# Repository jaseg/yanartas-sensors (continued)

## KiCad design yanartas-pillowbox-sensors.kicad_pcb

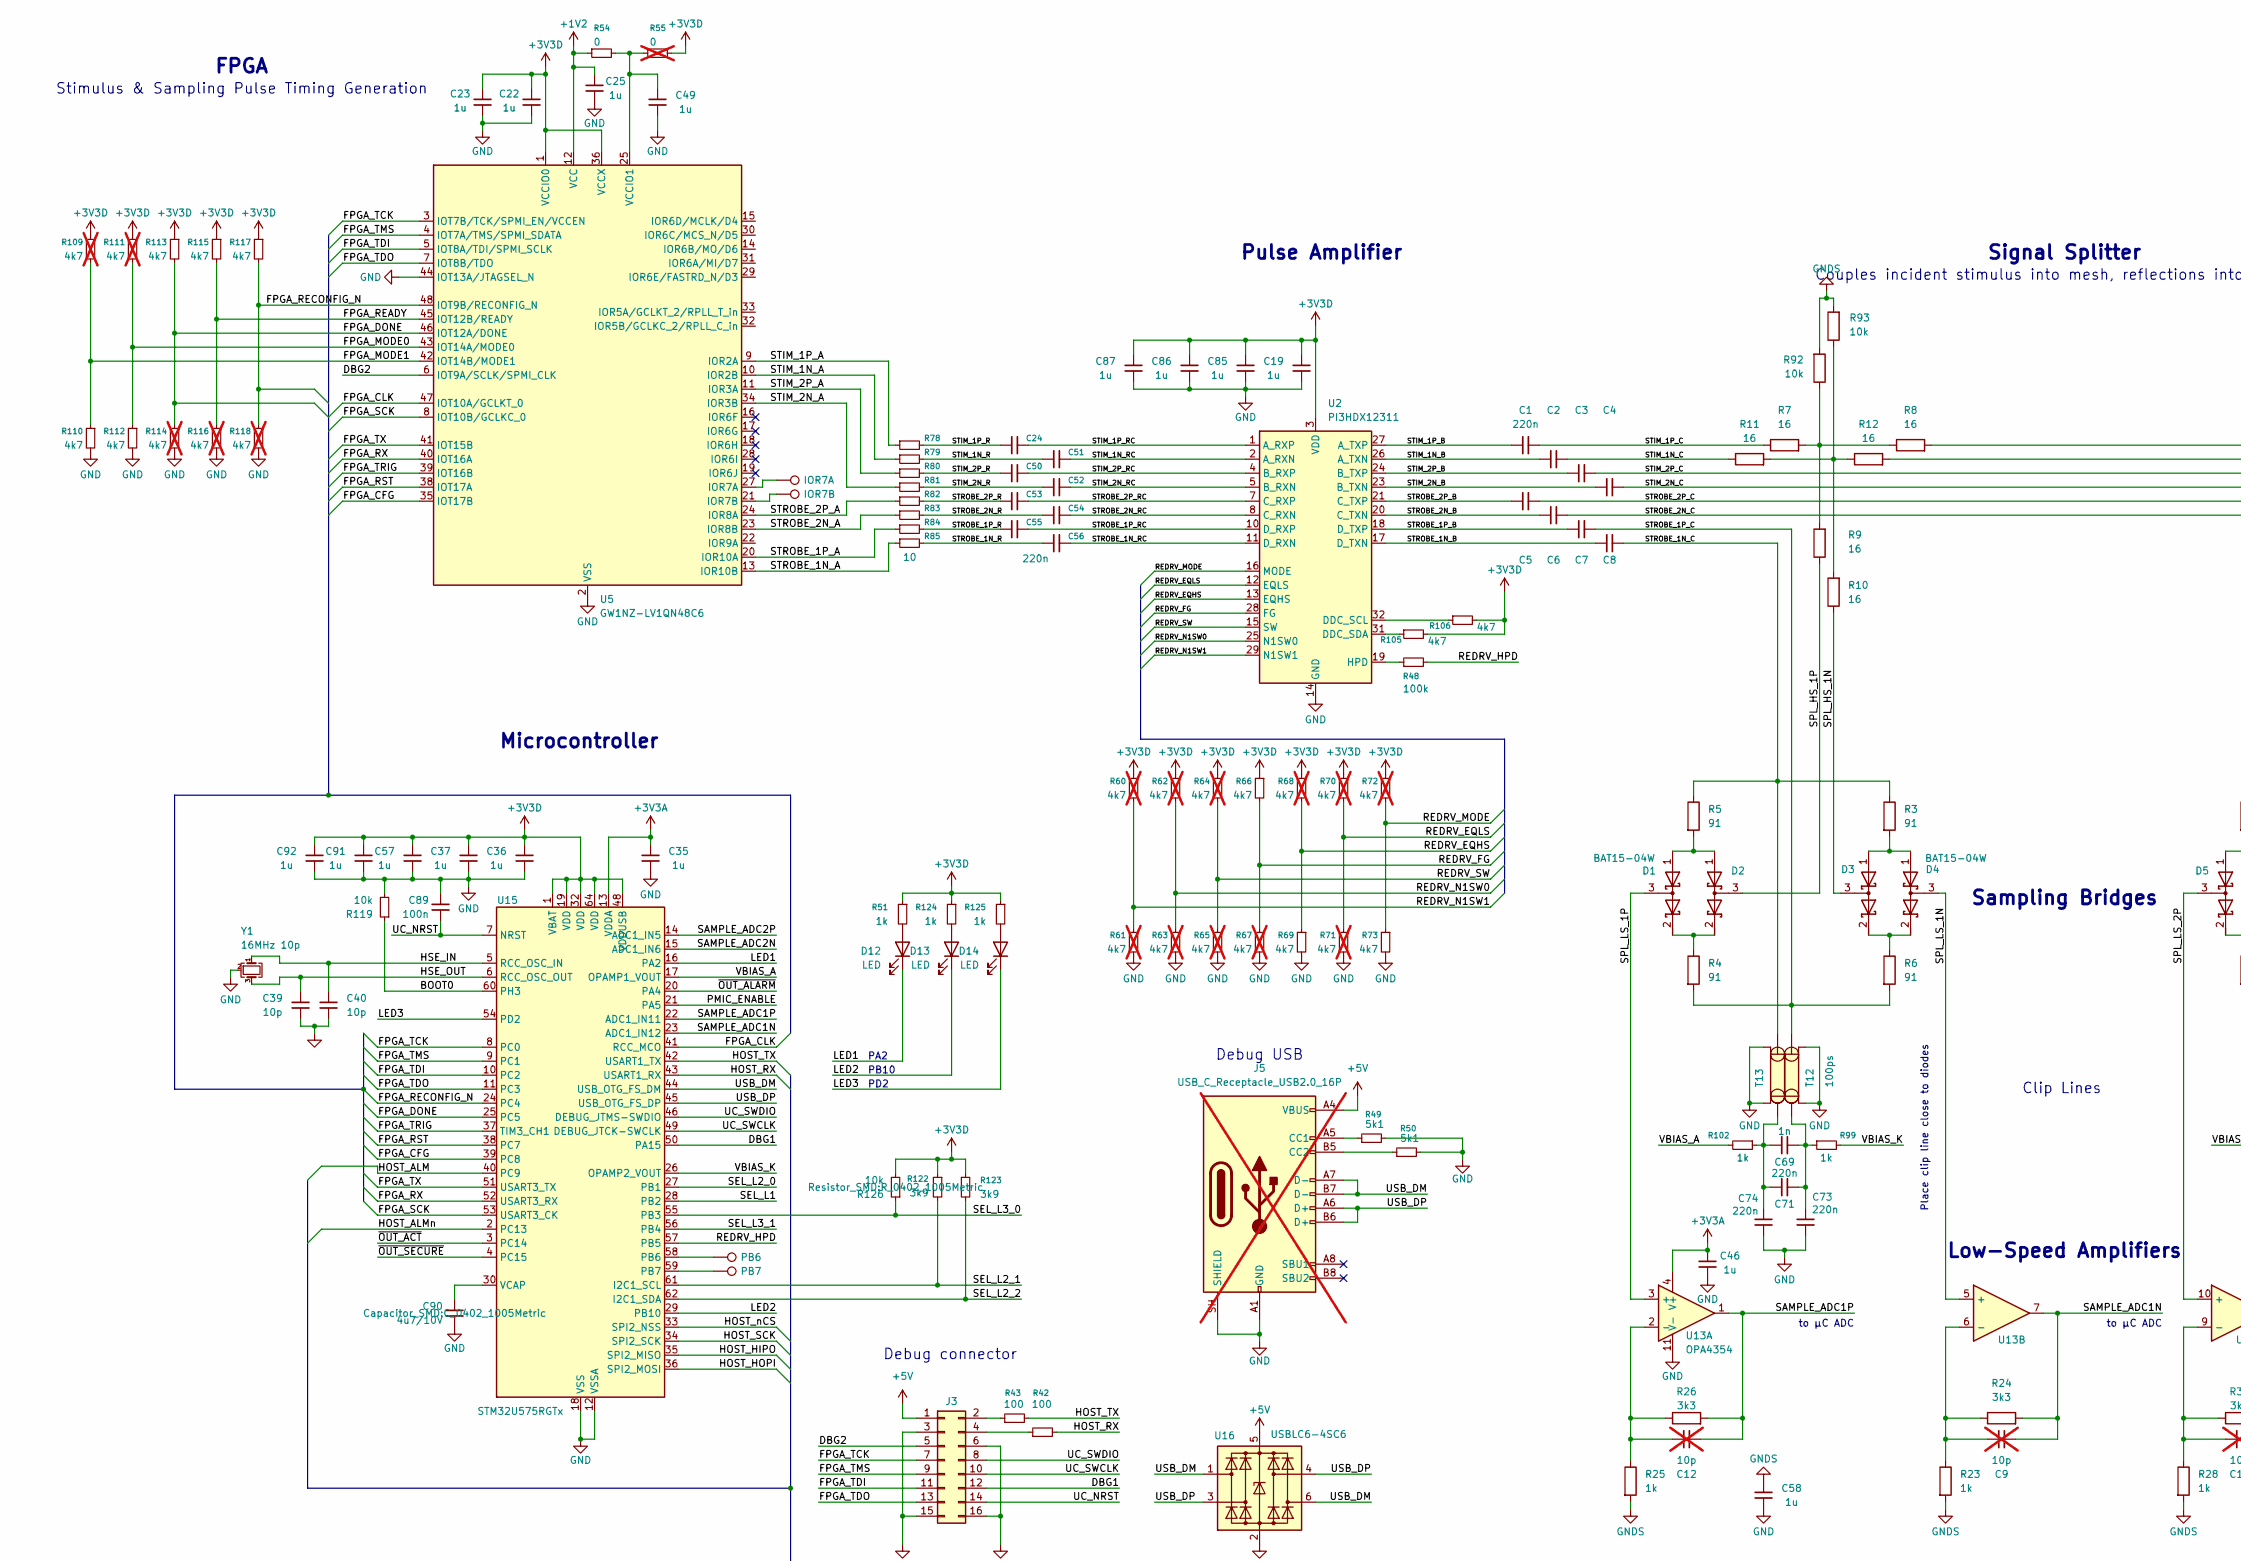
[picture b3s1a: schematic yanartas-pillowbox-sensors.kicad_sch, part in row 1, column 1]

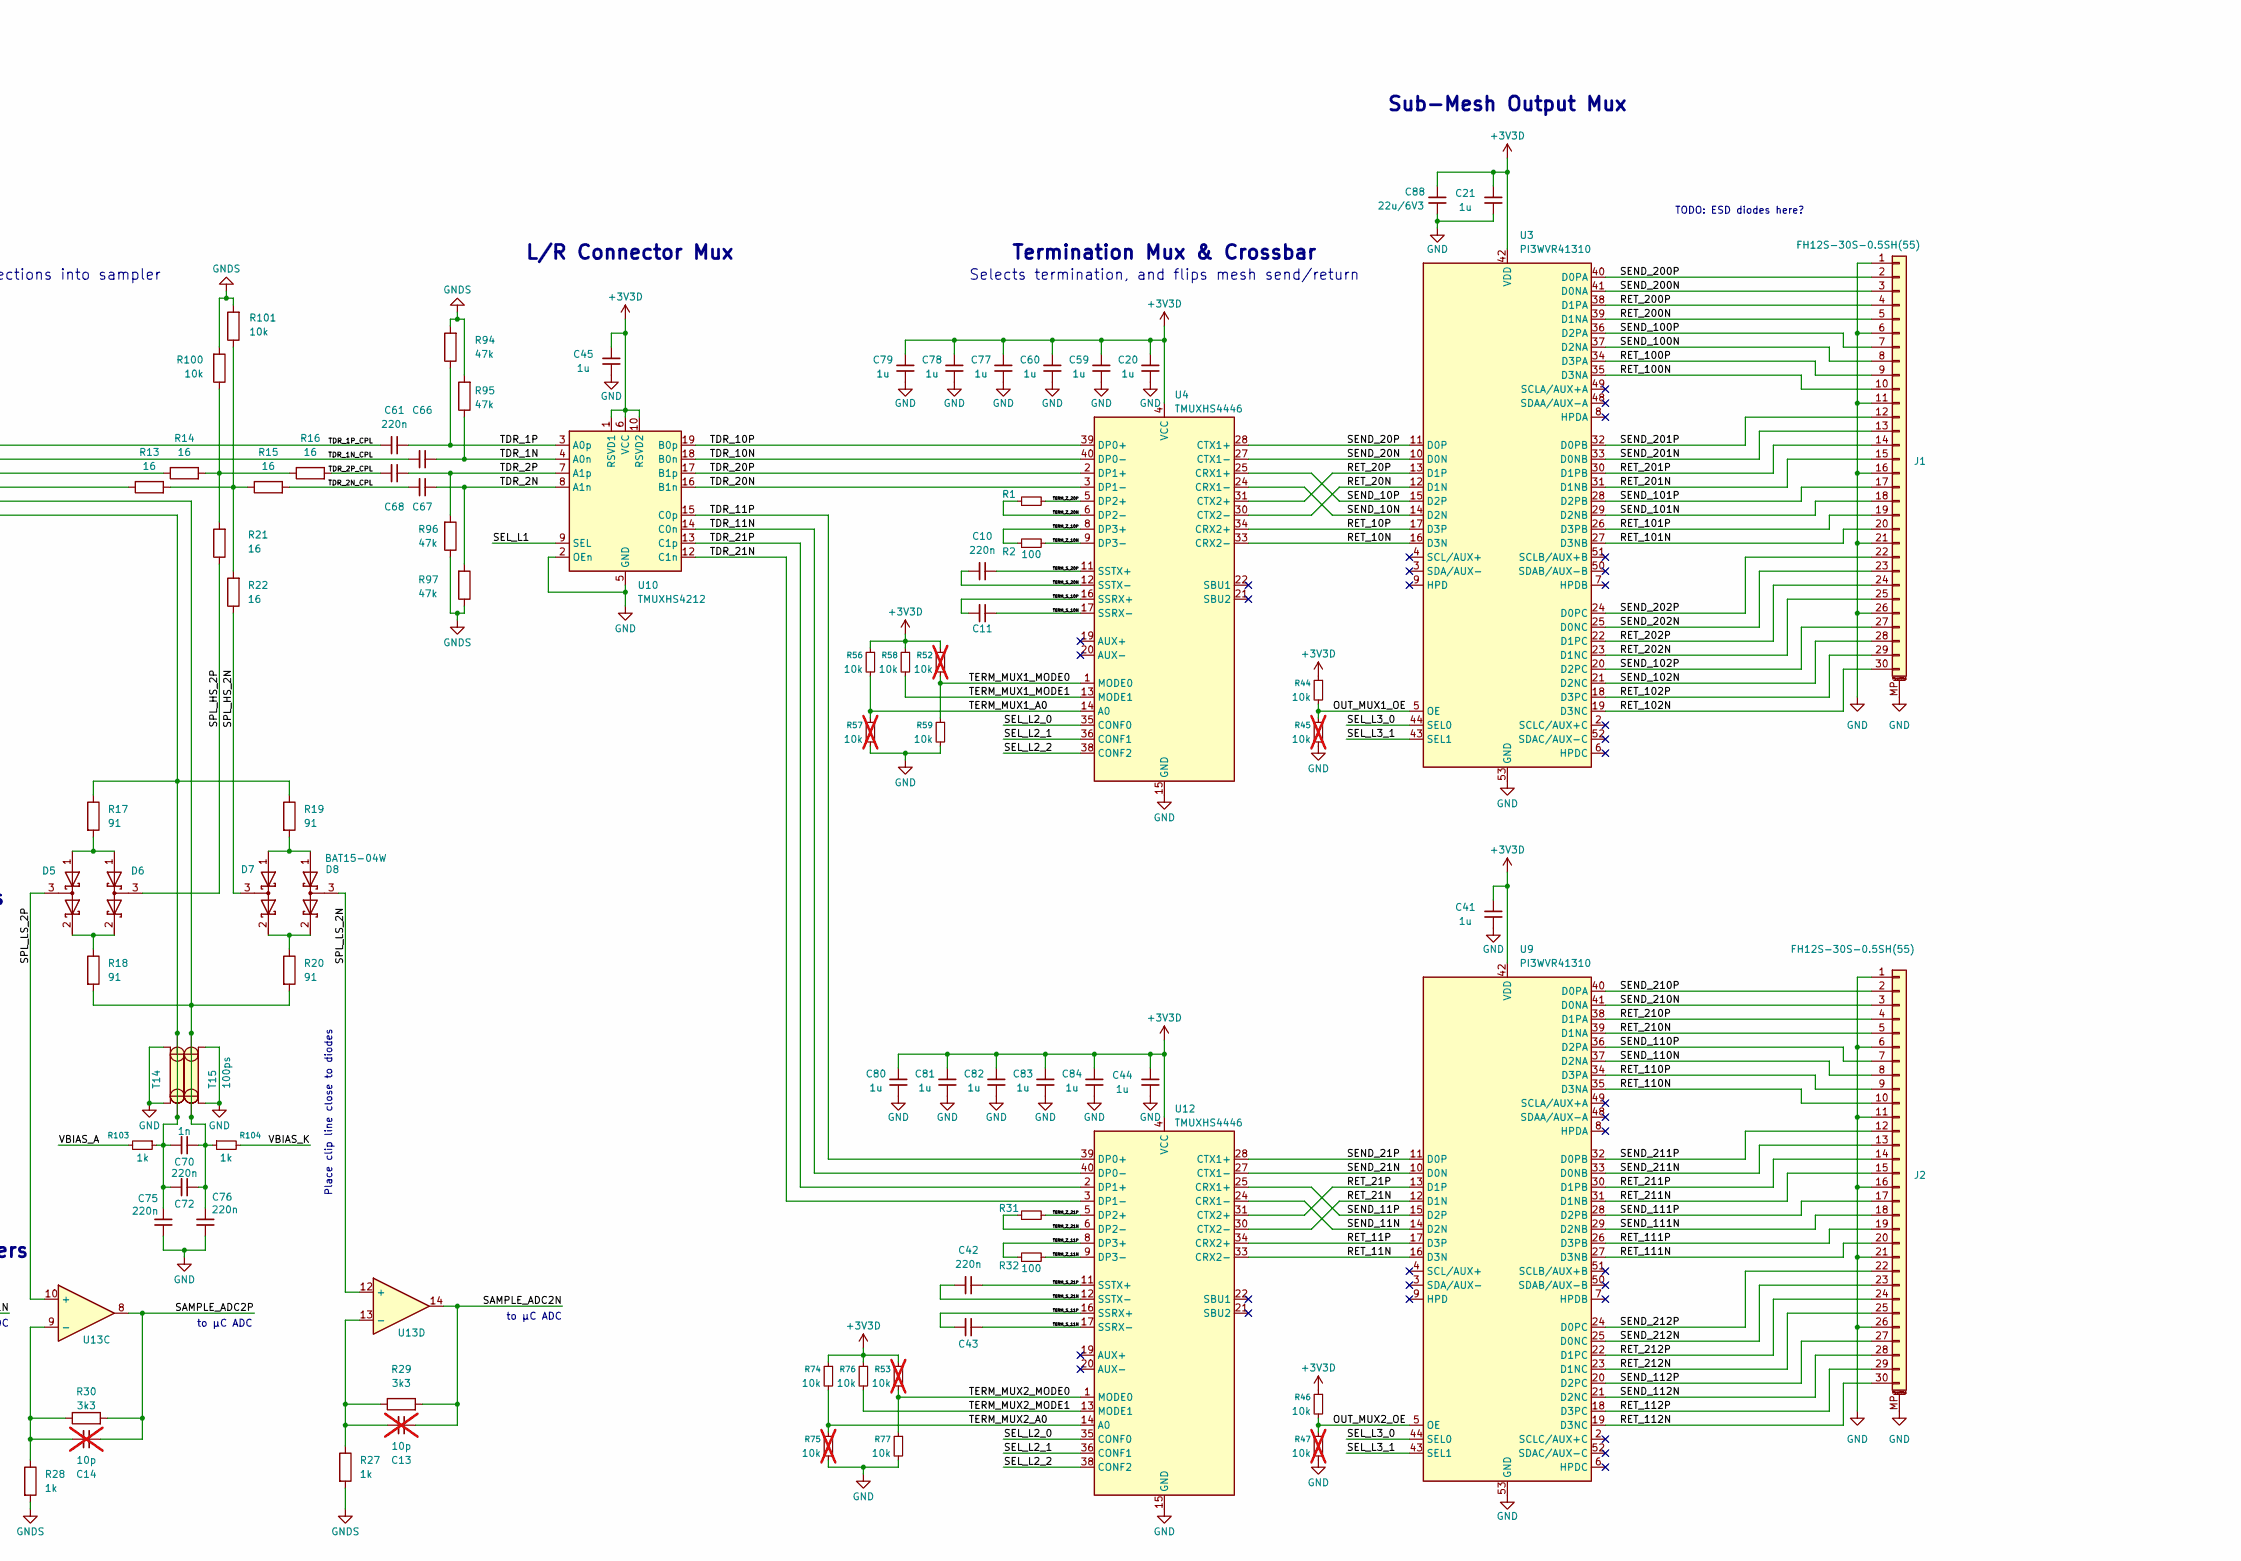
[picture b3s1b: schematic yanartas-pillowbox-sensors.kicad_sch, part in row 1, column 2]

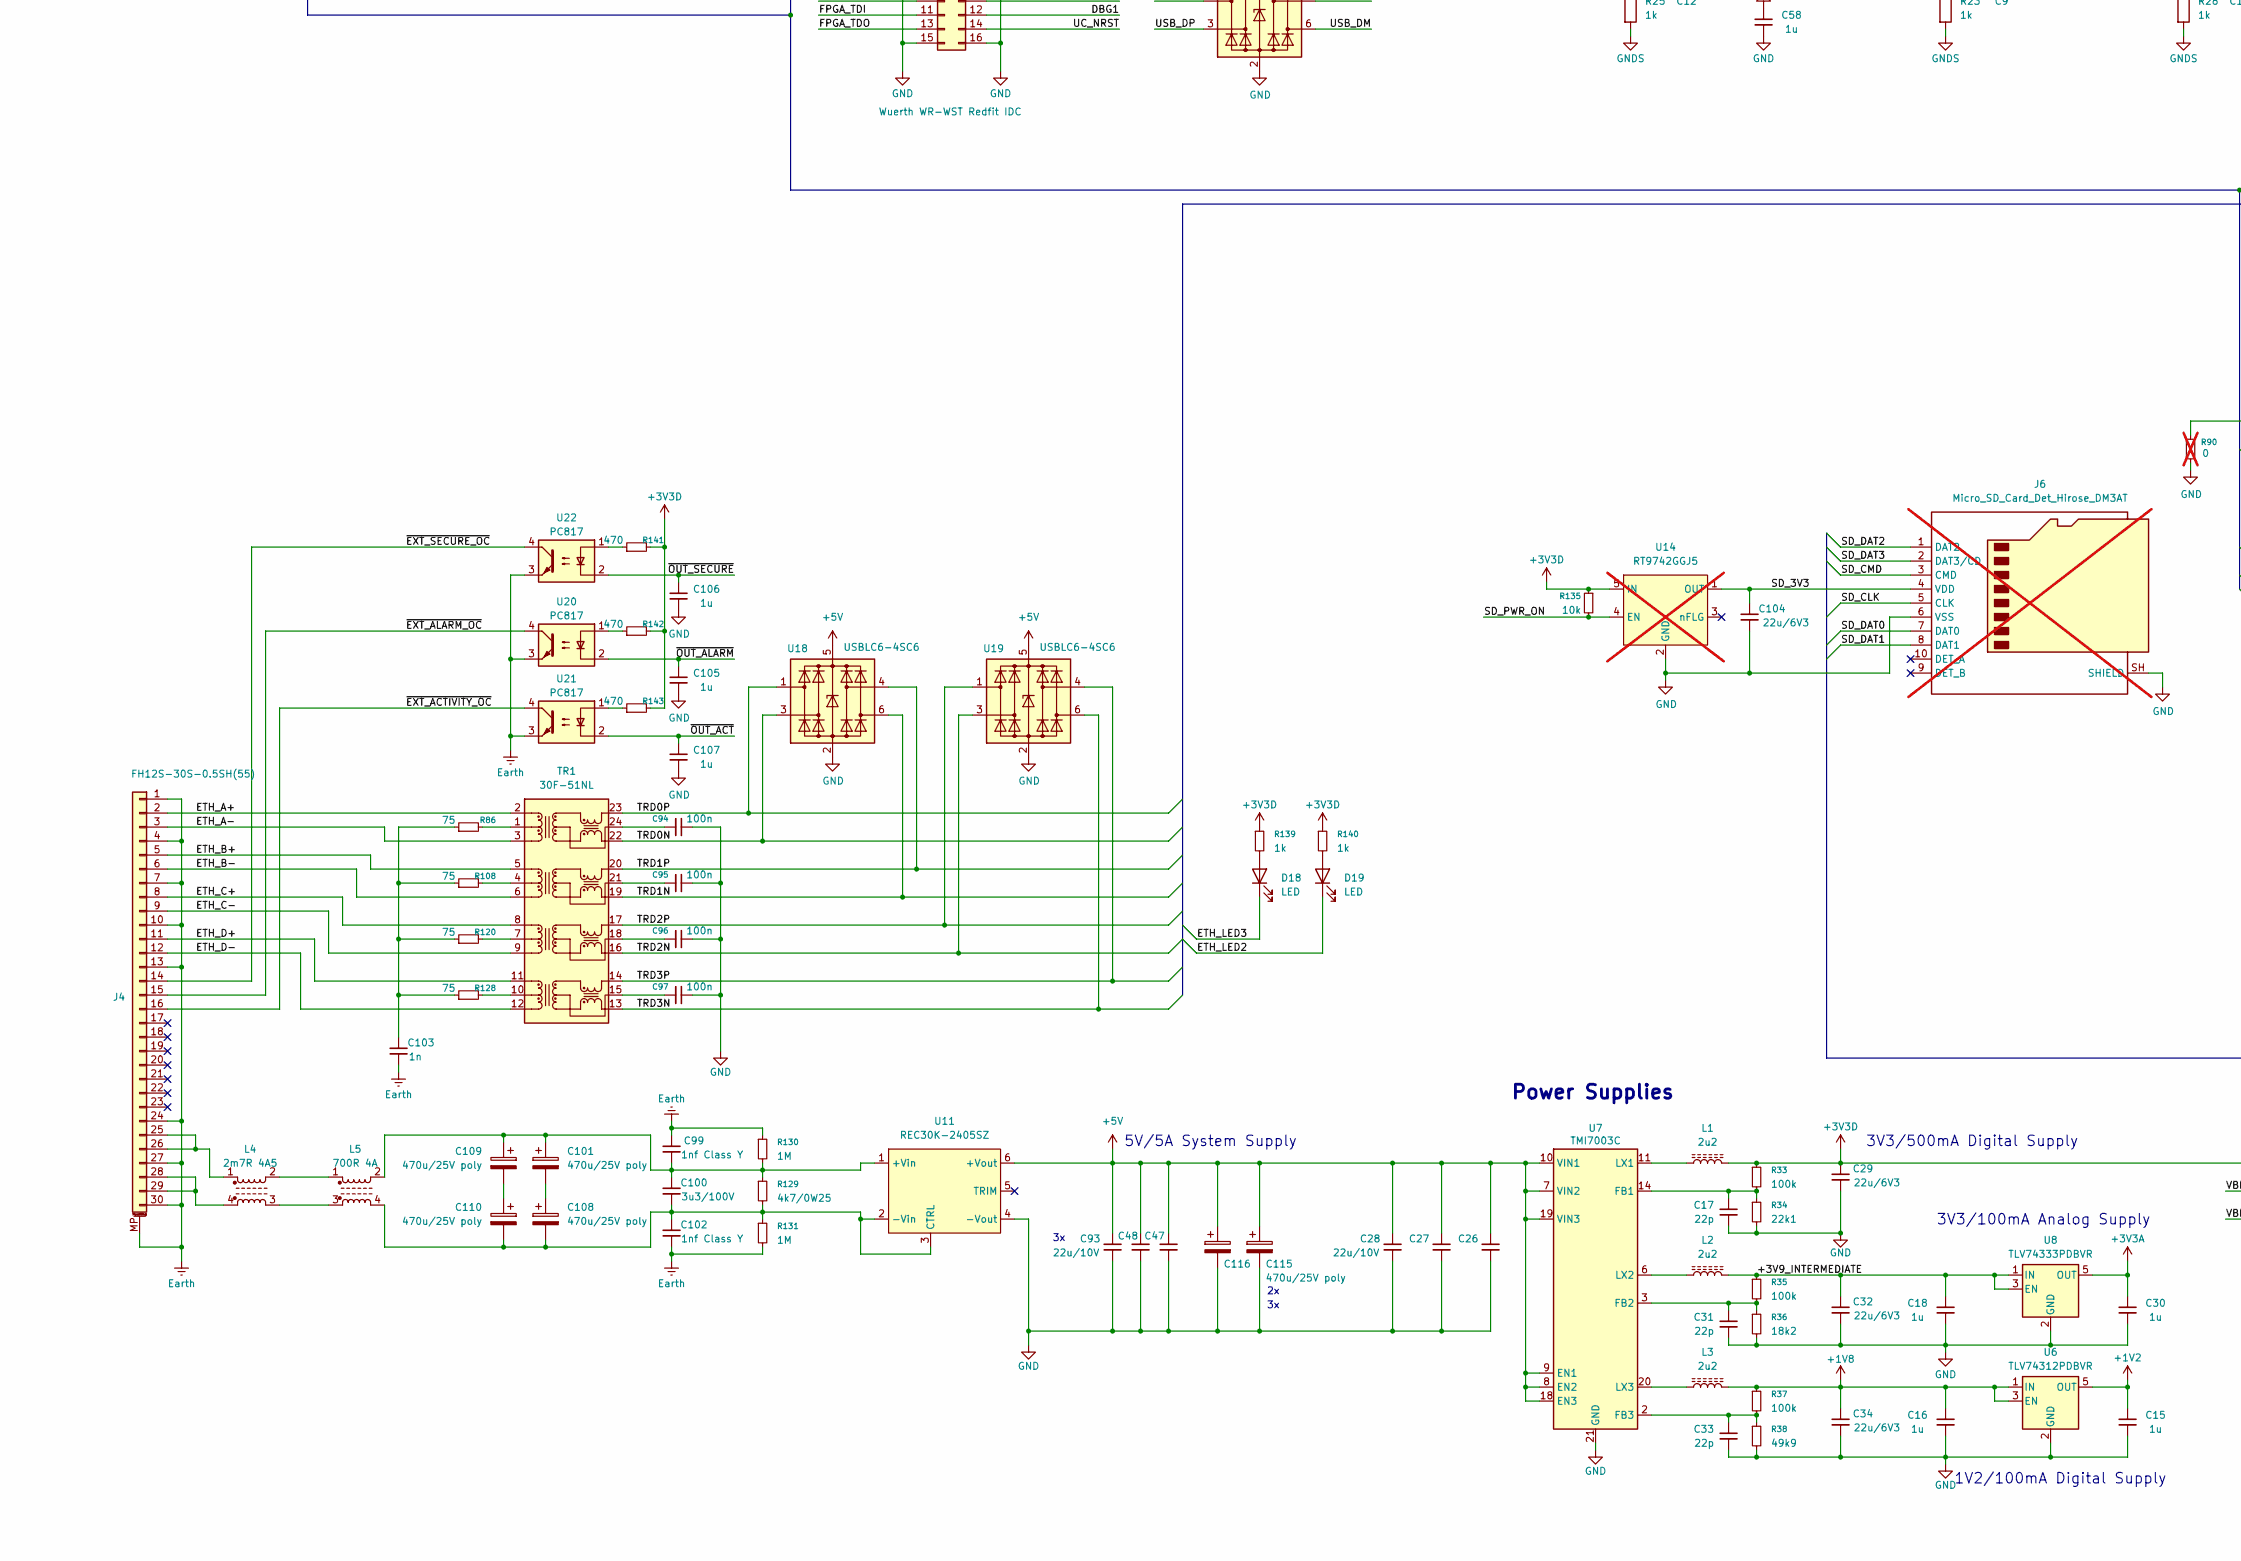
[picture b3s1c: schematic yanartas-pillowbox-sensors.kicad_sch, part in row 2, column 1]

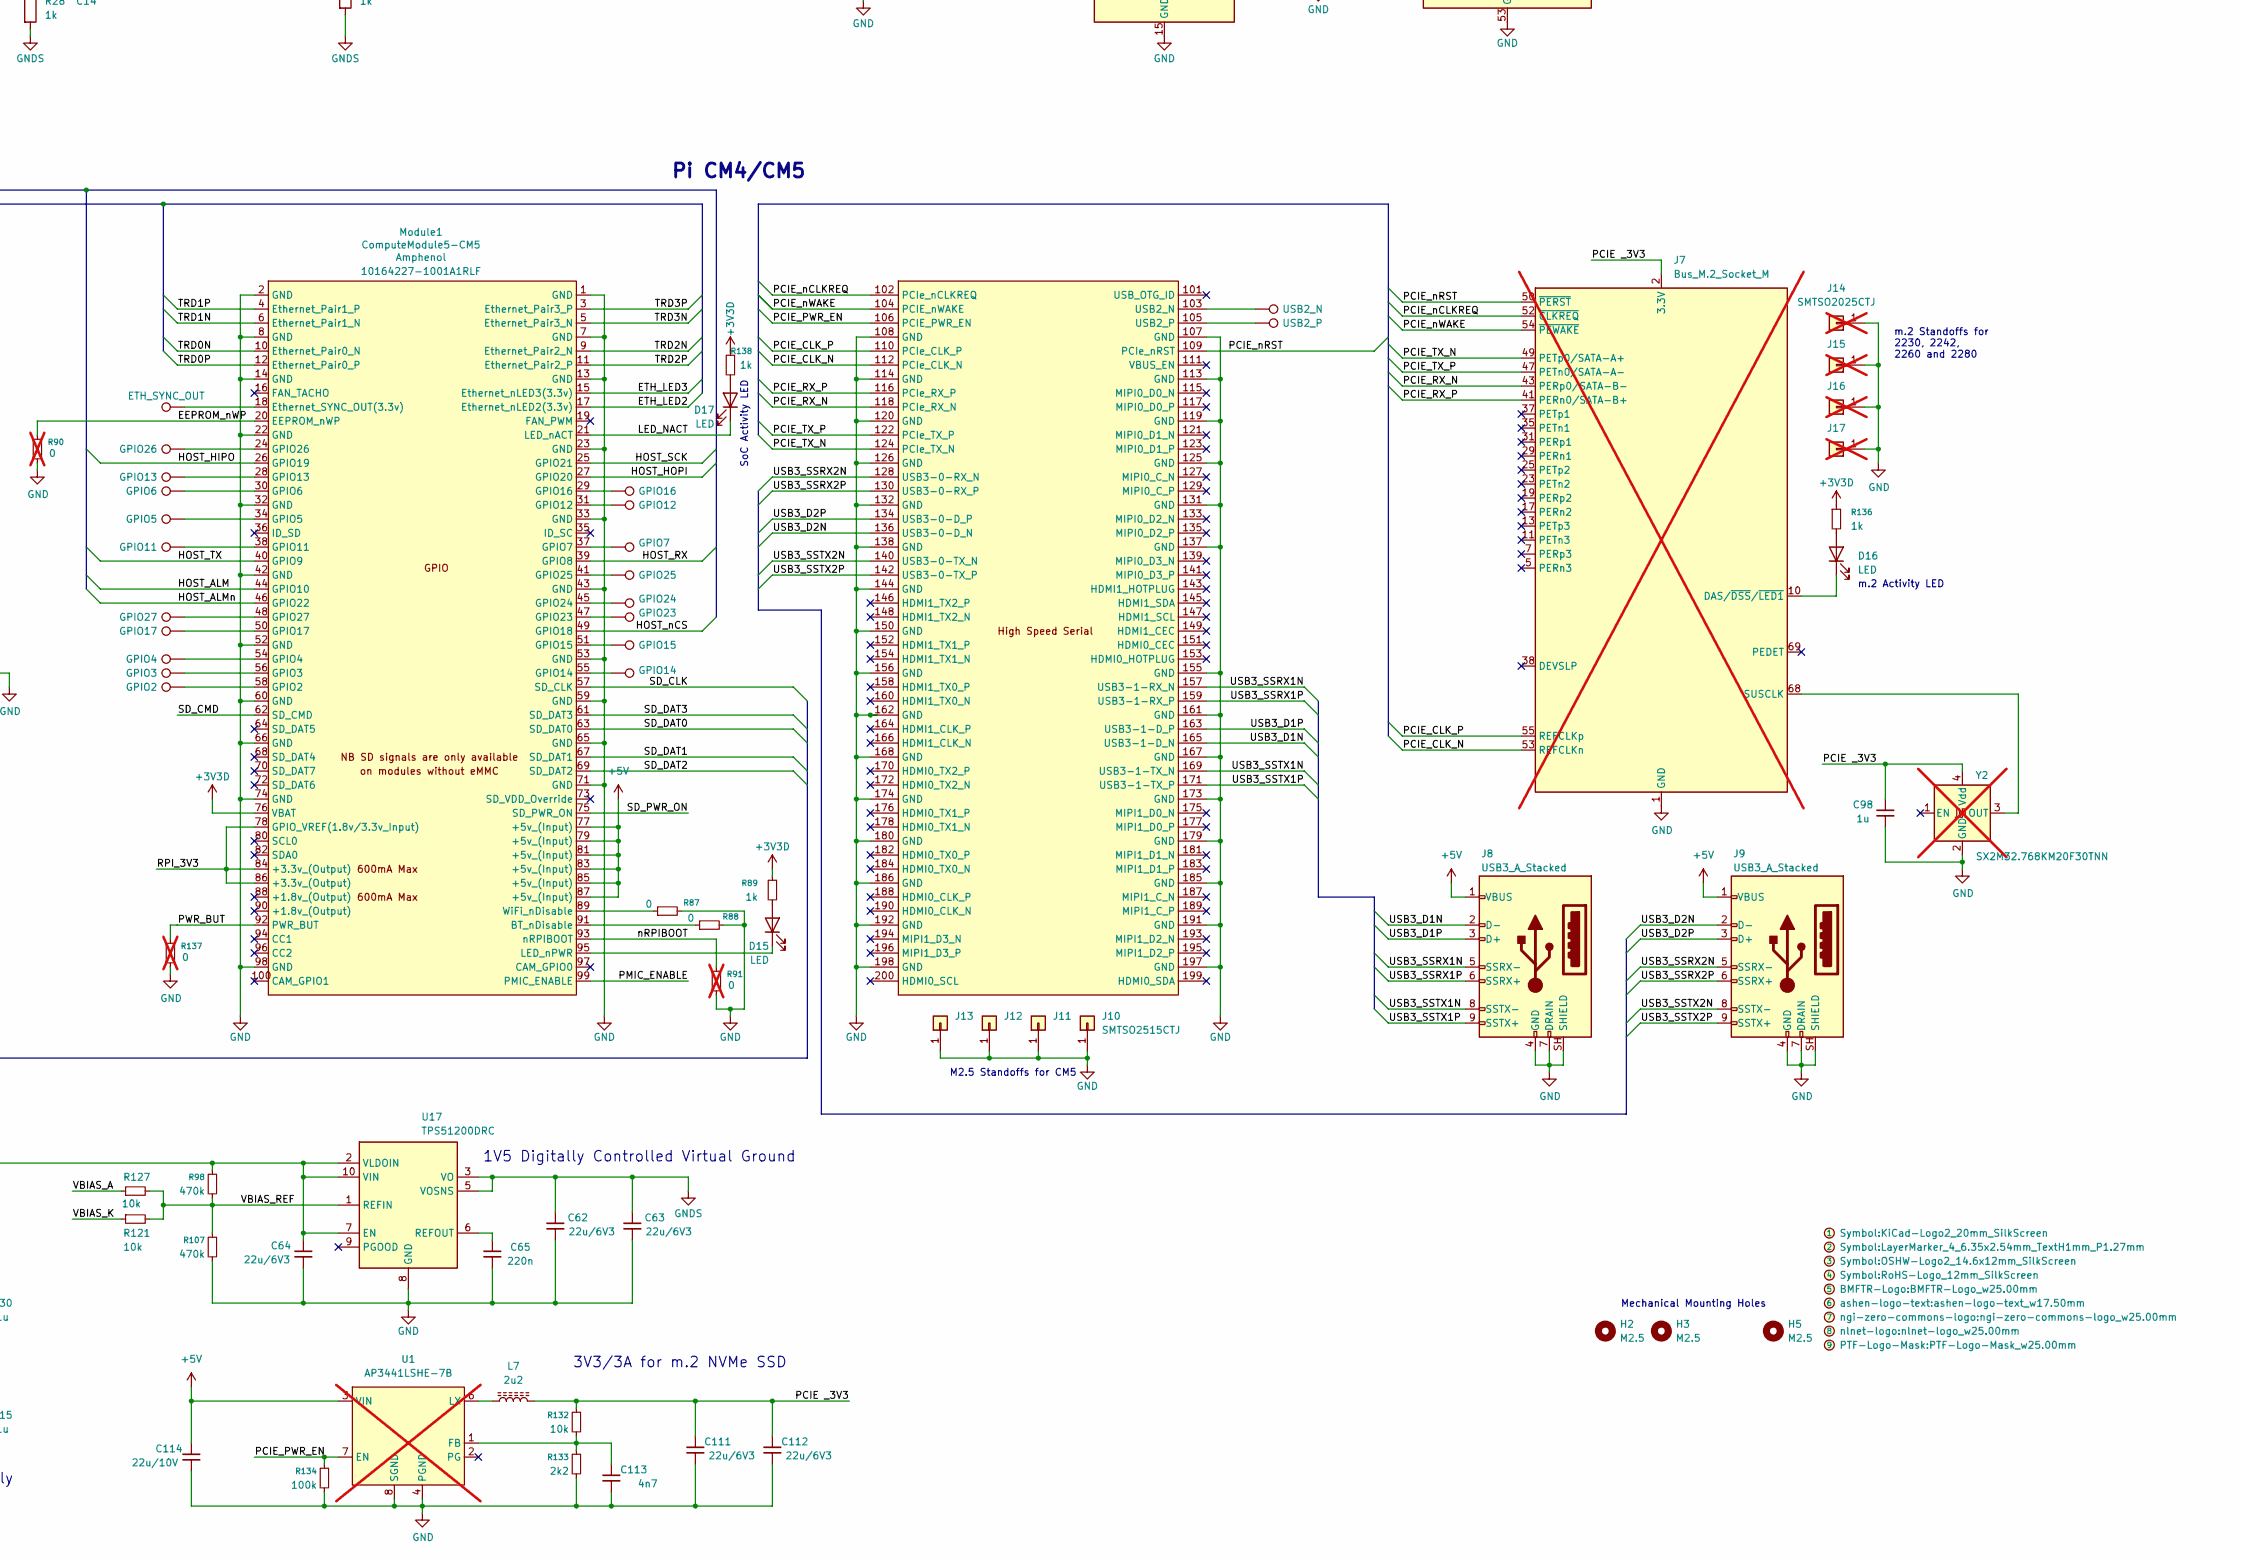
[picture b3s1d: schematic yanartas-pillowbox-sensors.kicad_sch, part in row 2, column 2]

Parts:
C1, C2, C3, C4, C5, C6, C7, C8, C10, C11, C24, C42, C43, C50, C51, C52, C53, C54, C55, C56, C61, C65, C66, C67, C68, C71, C72, C73, C74, C75, C76: 220n; C_0402_1005Metric; LCSC C16772
C9, C12, C13, C14: 10p; C_0402_1005Metric; LCSC C32949; not fitted
C15, C16, C18, C19, C20, C21, C22, C23, C25, C30, C35, C36, C37, C41, C44, C45, C46, C49, C57, C58, C59, C60, C77, C78, C79, C80, C81, C82, C83, C84, C85, C86, C87, C91, C92, C98, C105, C106, C107: 1u; C_0402_1005Metric; LCSC C52923
C17, C31, C33: 22p; C_0402_1005Metric; LCSC C1555
C26, C27: 10u/10V; C_0603_1608Metric; LCSC C96446
C28, C47, C48, C93, C114: 22u/10V; C_0805_2012Metric; LCSC C45783
C29, C32, C34, C62, C63, C64, C88, C104, C111, C112: 22u/6V3; C_0805_2012Metric; LCSC C45783
C39, C40: 10p; C_0402_1005Metric; LCSC C32949
C69, C70: 1n; C_0402_1005Metric; LCSC C1523
C89, C94, C95, C96, C97: 100n; C_0402_1005Metric; LCSC C1525
C90: 4u7/10V; C_0402_1005Metric; LCSC C23733
C99, C102: 1nf Class Y; C_Rect_L13.0mm_W4.0mm_P10.00mm_FKS3_FKP3_MKS4; LCSC C361361
C100: 3u3/100V; C_1206_3216Metric; LCSC C695361
C101, C108, C109, C110, C115, C116: 470u/25V poly; CP_Radial_D10.0mm_P5.00mm; MfgPN A750MS477M1EAAE015; LCSC C696345
C103: 1n; C_0603_1608Metric; LCSC C1588
C113: 4n7; C_0402_1005Metric; LCSC C1538
D1, D2, D3, D4, D5, D6, D7, D8: BAT15-04W; SOT-323_SC-70; LCSC C5380972
D12, D13, D14, D15, D16, D17, D18, D19: LED; LED_0603_1608Metric; LCSC C2290
H2, H3, H5: M2.5; MountingHole_2.7mm_M2.5; LCSC NA
J1, J2, J4: FH12S-30S-0.5SH(55); Hirose_FH12-30S-0.5SH_1x30-1MP_P0.50mm_Horizontal; LCSC C3169607
J3: Wuerth WR-WST Redfit IDC; Würth_WR-WST_debug_490107671612_2x08_P2.54mm_Vertical; LCSC NA
J5: USB_C_Receptacle_USB2.0_16P; USB_C_Receptacle_HRO_TYPE-C-31-M-12; LCSC C165948; not fitted
J6: Micro_SD_Card_Det_Hirose_DM3AT; microSD_HC_Hirose_DM3AT-SF-PEJM5; MPN DM3AT-SF-PEJM5; LCSC C114218; not fitted
J7: Bus_M.2_Socket_M; CONN-SMD_MDT420M02001; LCSC C2927698; not fitted
J8, J9: USB3_A_Stacked; USB_A_Receptacle_XKB_U231-091N-4BLRA00-S; LCSC C2880618
J10, J11, J12, J13: SMTSO2515CTJ; SINHOO_SMTSO25XX; LCSC C2915629
J14, J15, J16, J17: SMTSO2025CTJ; SINHOO_SMTSO20XX; LCSC C2916321; not fitted
L1, L2, L3, L7: 2u2; CJIANG_FXL0420; LCSC C167206
L4: 2m7R 4A5; EPCOS_B82723A; MPN B82723A2402N001; LCSC NA
L5: 700R 4A; TDK_ACM7060; MPN ACM7060-701-2PL-TL01; LCSC C78246
Module1: ComputeModule5-CM5; Raspberry-Pi-5-Compute-Module-A; Part Description 100 Position Connector Receptacle, Cent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; LCSC C6782225
Module2: ComputeModule5-CM5; Raspberry-Pi-5-Compute-Module-B; Part Description 100 Position Connector Receptacle, Cent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; LCSC C6782225
R1, R2, R31, R32, R42, R43: 100; R_0402_1005Metric; LCSC C25076
R3, R4, R5, R6, R17, R18, R19, R20: 91; R_0402_1005Metric; LCSC C4147
R7, R8, R9, R10, R11, R12, R13, R14, R15, R16, R21, R22: 16; R_0402_1005Metric; LCSC C227309
R23, R25, R27, R28, R51, R89, R99, R102, R103, R104, R124, R125, R136, R138, R139, R140: 1k; R_0402_1005Metric; LCSC C11702
R24, R26, R29, R30: 3k3; R_0402_1005Metric; LCSC C25890
R33, R35, R37, R48, R134: 100k; R_0402_1005Metric; LCSC C25741
R34: 22k1; R_0402_1005Metric; LCSC C25768
R36: 18k2; R_0402_1005Metric; LCSC C25762
R38: 49k9; R_0402_1005Metric; LCSC C25897
R44, R46, R56, R58, R59, R74, R76, R77, R92, R93, R100, R101, R119, R121, R126, R127, R132, R135: 10k; R_0402_1005Metric; LCSC C25744
R45, R47, R52, R53, R57, R75: 10k; R_0402_1005Metric; LCSC C25744; not fitted
R49, R50: 5k1; R_0402_1005Metric; LCSC C25905
R54, R87, R88: 0; R_0402_1005Metric; LCSC C17168
R55, R90, R91, R137: 0; R_0402_1005Metric; LCSC C17168; not fitted
R60, R61, R62, R63, R64, R65, R67, R68, R70, R71, R72, R109, R111, R114, R116, R118: 4k7; R_0402_1005Metric; LCSC C25900; not fitted
R66, R69, R73, R105, R106, R110, R112, R113, R115, R117: 4k7; R_0402_1005Metric; LCSC C25900
R78, R79, R80, R81, R82, R83, R84, R85: 10; R_0402_1005Metric; LCSC C25077
R86, R108, R120, R128: 75; R_0402_1005Metric; LCSC C25133
R94, R95, R96, R97: 47k; R_0402_1005Metric; LCSC C25792
R98, R107: 470k; R_0402_1005Metric; LCSC C25790
R122, R123: 3k9; R_0402_1005Metric; LCSC C51721
R129: 4k7/0W25; R_1206_3216Metric; LCSC C17936
R130, R131: 1M; R_0603_1608Metric; LCSC C22935
R133: 2k2; R_0402_1005Metric; LCSC C25879
R141, R142, R143: 470; R_0402_1005Metric; LCSC C23179
T12, T13, T14, T15: 100ps; LCSC NA
TP1: GPIO27; TestPoint_Pad_D1.0mm; LCSC NA
TP2: GPIO17; TestPoint_Pad_D1.0mm; LCSC NA
TP3: GPIO4; TestPoint_Pad_D1.0mm; LCSC NA
TP4: GPIO3; TestPoint_Pad_D1.0mm; LCSC NA
TP5: GPIO2; TestPoint_Pad_D1.0mm; LCSC NA
TP6: GPIO11; TestPoint_Pad_D1.0mm; LCSC NA
TP7: GPIO5; TestPoint_Pad_D1.0mm; LCSC NA
TP8: GPIO6; TestPoint_Pad_D1.0mm; LCSC NA
TP9: GPIO13; TestPoint_Pad_D1.0mm; LCSC NA
TP10: GPIO26; TestPoint_Pad_D1.0mm; LCSC NA
TP11: ETH_SYNC_OUT; TestPoint_Pad_D1.0mm; LCSC NA
TP12: GPIO14; TestPoint_Pad_D1.0mm; LCSC NA
TP13: GPIO15; TestPoint_Pad_D1.0mm; LCSC NA
TP14: GPIO23; TestPoint_Pad_D1.0mm; LCSC NA
TP15: GPIO24; TestPoint_Pad_D1.0mm; LCSC NA
TP16: GPIO25; TestPoint_Pad_D1.0mm; LCSC NA
TP17: GPIO7; TestPoint_Pad_D1.0mm; LCSC NA
TP18: GPIO12; TestPoint_Pad_D1.0mm; LCSC NA
TP19: GPIO16; TestPoint_Pad_D1.0mm; LCSC NA
TP20: USB2_N; TestPoint_Pad_D1.0mm; LCSC NA
TP21: USB2_P; TestPoint_Pad_D1.0mm; LCSC NA
TP22: IOR7A; TestPoint_Pad_D1.0mm; LCSC NA
TP23: IOR7B; TestPoint_Pad_D1.0mm; LCSC NA
TP24: PB6; TestPoint_Pad_D1.0mm; LCSC NA
TP25: PB7; TestPoint_Pad_D1.0mm; LCSC NA
TR1: 30F-51NL; Transformer_Ethernet_YDS_30F-51NL_SO-24_7.1x15.1mm; LCSC C123168
U1: AP3441LSHE-7B; DFN-8-1EP_2x2mm_P0.5mm_EP1.05x1.75mm; LCSC` C2072094; not fitted
U2: PI3HDX12311; Diodes_XEA32_X1-QFN-32-1EP_2.85x4.5mm_P0.4mm_EP1.75x3.4mm; Digikey 31-PI3HDX12311XEAEXCT-ND
U3, U9: PI3WVR41310; Diodes_ZL52_TQFN-52-1EP_3.5x9mm_P0.4mm_EP2.3x7.8mm; Digikey 31-PI3WVR41310ZLEXCT-ND
U4, U12: TMUXHS4446; Texas_RET0040A_WQFN-40-1EP_3x6mm_P0.4mm_EP1.7x4.5mm; Digikey 296-TMUXHS4446IRETRCT-ND
U5: GW1NZ-LV1QN48C6; Gowin_QN48_QFN-48-1EP_6x6mm_P0.4mm_EP4.2x4.2mm; LCSC C5799569
U6: TLV74312PDBVR; SOT-23-5; LCSC C485149
U7: TMI7003C; Toll_QFN-20-1EP_3x3mm_P0.4mm_EP1.7x1.7mm; LCSC C840566
U8: TLV74333PDBVR; SOT-23-5; LCSC C51953291
U10: TMUXHS4212; Texas_RKS0020A_VQFN-20-1EP_2.5x4.5mm_P0.5mm_EP1x3mm; LCSC C2869871
U11: REC30K-2405SZ; RECOM_REC30K-2405SZ; LCSC NA
U13: OPA4354; SOIC-14_3.9x8.7mm_P1.27mm; LCSC C527494
U14: RT9742GGJ5; SOT-23-5; Part Description Power Switch/Driver 1:1 N-Channel 1A TS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; LCSC C250547; not fitted
U15: STM32U575RGTx; LQFP-64_10x10mm_P0.5mm; Digikey 497-STM32U575RGT6TRCT-ND
U16, U18, U19: USBLC6-4SC6; SOT-23-6; LCSC C558419
U17: TPS51200DRC; VSON-10-1EP_3x3mm_P0.5mm_EP1.65x2.4mm; LCSC C34771
U20, U21, U22: PC817; SMDIP-4_W7.62mm; LCSC C41807
Y1: 16MHz 10p; Crystal_SMD_3225-4Pin_3.2x2.5mm; LCSC C13738
Y2: SX2M32.768KM20F30TNN; Crystal_SMD_2520-4Pin_2.5x2.0mm; LCSC C2901603; not fitted

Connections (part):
+1V2: C15.2, C25.2, R54.1, U5.12 (VCC), U5.37 (VCC), U6.5 (OUT)
+1V8: C16.2, C34.2, L3.2, R37.1, U6.1 (IN), U6.3 (EN)
+3V3A: C30.2, C35.2, C46.2, U8.5 (OUT), U13.4 (V+), U15.13 (VDDA)
+3V3D: C19.2, C20.2, C21.2, C22.2, C23.2, C29.2, C36.2, C37.2, C41.2, C44.2, C45.2, C57.2, C59.2, C60.2, C64.2, C77.2, C78.2, C79.2, C80.2, C81.2, C82.2, C83.2, C84.2, C85.2, C86.2, C87.2, C88.2, C91.2, C92.2, L1.2, Module1.76 (VBAT), R33.1, R44.1, R46.1, R51.1, R52.1, R53.1, R55.2, R56.1, R58.1, R60.1, R62.1, R64.1, R66.1, R68.1, R70.1, R72.1, R74.1, R76.1, R89.1, R98.1, R105.2, R106.2, R109.1, R111.1, R113.1, R115.1, R117.1, R122.1, R123.1, R124.1, R125.1, R126.2, R135.1, R136.1, R138.1, R139.1, R140.1, R141.2, R142.2, R143.2, U2.3 (VDD), U2.6 (VDD), U2.9 (VDD), U2.22 (VDD), U3.42 (VDD), U4.4 (VCC), U4.7 (VCC), U4.10 (VCC), U4.23 (VCC)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
+5V: C26.2, C27.2, C28.2, C47.2, C48.2, C93.2, C114.2, C115.1, C116.1, J3.1, J5.A4 (VBUS), J5.A9 (VBUS), J5.B4 (VBUS), J5.B9 (VBUS), J8.1 (VBUS), J9.1 (VBUS), Module1.77 (+5v_(Input)), Module1.79 (+5v_(Input)), Module1.81 (+5v_(Input)), Module1.83 (+5v_(Input)), Module1.85 (+5v_(Input)), Module1.87 (+5v_(Input)), U1.3 (VIN), U7.7 (VIN2), U7.8 (EN2), U7.9 (EN1), U7.10 (VIN1), U7.18 (EN3), U7.19 (VIN3), U11.6 (+Vout), U16.5 (VBUS), U18.5 (VBUS), U19.5 (VBUS)
/+3V9_INTERMEDIATE: C18.2, C32.2, L2.2, R35.1, U8.1 (IN), U8.3 (EN)
/BOOT0: R119.1, U15.60 (PH3)
/DBG1: J3.12, U15.50 (PA15)
/DBG2: J3.5, U5.6 (IOT9A/SCLK/SPMI_CLK)
/EEPROM_nWP: Module1.20 (EEPROM_nWP), R90.2
/ETH_A+: J4.2, TR1.2 (TD1+)
/ETH_A-: J4.3, TR1.3 (TD1-)
/ETH_B+: J4.5, TR1.5 (TD2+)
/ETH_B-: J4.6, TR1.6 (TD2-)
/ETH_C+: J4.8, TR1.8 (TD3+)
/ETH_C-: J4.9, TR1.9 (TD3-)
/ETH_D+: J4.11, TR1.11 (TD4+)
/ETH_D-: J4.12, TR1.12 (TD4-)
/ETH_LED2: D19.1 (K), Module1.17 (Ethernet_nLED2(3.3v))
/ETH_LED3: D18.1 (K), Module1.15 (Ethernet_nLED3(3.3v))
/FPGA_CFG: U5.35 (IOT17B), U15.39 (PC8)
/FPGA_CLK: U5.47 (IOT10A/GCLKT_0), U15.41 (RCC_MCO)
/FPGA_DONE: R113.2, R114.1, U5.46 (IOT12A/DONE), U15.25 (PC5)
/FPGA_MODE0: R111.2, R112.1, U5.43 (IOT14A/MODE0)
/FPGA_MODE1: R109.2, R110.1, U5.42 (IOT14B/MODE1)
/FPGA_READY: R115.2, R116.1, U5.45 (IOT12B/READY)
/FPGA_RECONFIG_N: R117.2, R118.1, U5.48 (IOT9B/RECONFIG_N), U15.24 (PC4)
/FPGA_RST: U5.38 (IOT17A), U15.38 (PC7)
/FPGA_RX: U5.40 (IOT16A), U15.52 (USART3_RX)
/FPGA_SCK: U5.8 (IOT10B/GCLKC_0), U15.53 (USART3_CK)
/FPGA_TCK: J3.7, U5.3 (IOT7B/TCK/SPMI_EN/VCCEN), U15.8 (PC0)
/FPGA_TDI: J3.11, U5.5 (IOT8A/TDI/SPMI_SCLK), U15.10 (PC2)
/FPGA_TDO: J3.13, U5.7 (IOT8B/TDO), U15.11 (PC3)
/FPGA_TMS: J3.9, U5.4 (IOT7A/TMS/SPMI_SDATA), U15.9 (PC1)
/FPGA_TRIG: U5.39 (IOT16B), U15.37 (TIM3_CH1)
/FPGA_TX: U5.41 (IOT15B), U15.51 (USART3_TX)
/HOST_ALM: Module1.44 (GPIO10), U15.40 (PC9)
/HOST_ALMn: Module1.46 (GPIO22), U15.2 (PC13)
/HOST_HIPO: Module1.26 (GPIO19), U15.35 (SPI2_MISO)
/HOST_HOPI: Module1.27 (GPIO20), U15.36 (SPI2_MOSI)
/HOST_RX: Module1.39 (GPIO8), R42.2, U15.43 (USART1_RX)
/HOST_SCK: Module1.25 (GPIO21), U15.34 (SPI2_SCK)
/HOST_TX: Module1.40 (GPIO9), R43.2, U15.42 (USART1_TX)
/HOST_nCS: Module1.49 (GPIO18), U15.33 (SPI2_NSS)
/HSE_IN: C40.2, U15.5 (RCC_OSC_IN), Y1.1
/HSE_OUT: C39.2, U15.6 (RCC_OSC_OUT), Y1.3
/LED1: D12.1 (K), U15.16 (PA2)
/LED2: D13.1 (K), U15.29 (PB10)
/LED3: D14.1 (K), U15.54 (PD2)
/LED_NACT: D17.1 (K), Module1.21 (LED_nACT)
/OUT_MUX1_OE: R44.2, R45.1, U3.5 (OE)
/OUT_MUX2_OE: R46.2, R47.1, U9.5 (OE)
/PCIE _3V3: C98.2, C111.2, C112.2, J7.2 (3.3V), J7.4 (3.3V), J7.12 (3.3V), J7.14 (3.3V), J7.16 (3.3V), J7.18 (3.3V), J7.70 (3.3V), J7.72 (3.3V), J7.74 (3.3V), L7.2, R132.1, Y2.4 (Vdd)
/PCIE_CLK_N: J7.53 (REFCLKn), Module2.112 (PCIe_CLK_N)
/PCIE_CLK_P: J7.55 (REFCLKp), Module2.110 (PCIe_CLK_P)
/PCIE_PWR_EN: Module2.106 (PCIE_PWR_EN), R134.1, U1.7 (EN)
/PCIE_RX_N: J7.43 (PERp0/SATA-B-), Module2.118 (PCIe_RX_N)
/PCIE_RX_P: J7.41 (PERn0/SATA-B+), Module2.116 (PCIe_RX_P)
/PCIE_TX_N: J7.49 (PETp0/SATA-A+), Module2.124 (PCIe_TX_N)
/PCIE_TX_P: J7.47 (PETn0/SATA-A-), Module2.122 (PCIe_TX_P)
/PCIE_nCLKREQ: J7.52 (~CLKREQ), Module2.102 (PCIe_nCLKREQ)
/PCIE_nRST: J7.50 (~PERST), Module2.109 (PCIe_nRST)
/PCIE_nWAKE: J7.54 (~PEWAKE), Module2.104 (PCIE_nWAKE)
/PMIC_ENABLE: Module1.99 (PMIC_ENABLE), U15.21 (PA5)
/PWR_BUT: Module1.92 (PWR_BUT), R137.2
/REDRV_EQHS: R68.2, R69.1, U2.13 (EQHS)
/REDRV_EQLS: R70.2, R71.1, U2.12 (EQLS)
/REDRV_FG: R66.2, R67.1, U2.28 (FG)
/REDRV_HPD: R48.2, U15.57 (PB5)
/REDRV_MODE: R72.2, R73.1, U2.16 (MODE)
/REDRV_N1SW0: R62.2, R63.1, U2.25 (N1SW0)
/REDRV_N1SW1: R60.2, R61.1, U2.29 (N1SW1)
/REDRV_SW: R64.2, R65.1, U2.15 (SW)
/RET_100N: J1.10, U3.35 (D3NA)
/RET_100P: J1.9, U3.34 (D3PA)
/RET_101N: J1.20, U3.27 (D3NB)
/RET_101P: J1.19, U3.26 (D3PB)
/RET_102N: J1.30, U3.19 (D3NC)
/RET_102P: J1.29, U3.18 (D3PC)
/RET_110N: J2.10, U9.35 (D3NA)
/RET_110P: J2.9, U9.34 (D3PA)
/RET_111N: J2.20, U9.27 (D3NB)
/RET_111P: J2.19, U9.26 (D3PB)
/RET_112N: J2.30, U9.19 (D3NC)
/RET_112P: J2.29, U9.18 (D3PC)
/RET_200N: J1.5, U3.39 (D1NA)
/RET_200P: J1.4, U3.38 (D1PA)
/RET_201N: J1.15, U3.31 (D1NB)
/RET_201P: J1.14, U3.30 (D1PB)
/RET_202N: J1.25, U3.23 (D1NC)
/RET_202P: J1.24, U3.22 (D1PC)
/RET_210N: J2.5, U9.39 (D1NA)
/RET_210P: J2.4, U9.38 (D1PA)
/RET_211N: J2.15, U9.31 (D1NB)
/RET_211P: J2.14, U9.30 (D1PB)
/RET_212N: J2.25, U9.23 (D1NC)
/RET_212P: J2.24, U9.22 (D1PC)
/RPI_3V3: Module1.78 (GPIO_VREF(1.8v/3.3v_Input)), Module1.84 (+3.3v_(Output)), Module1.86 (+3.3v_(Output))
/SAMPLE_ADC1N: C9.2, R24.2, U13.7, U15.23 (ADC1_IN12)
/SAMPLE_ADC1P: C12.2, R26.2, U13.1, U15.22 (ADC1_IN11)
/SAMPLE_ADC2N: C13.2, R29.2, U13.14, U15.15 (ADC1_IN6)
/SAMPLE_ADC2P: C14.2, R30.2, U13.8, U15.14 (ADC1_IN5)
/SD_3V3: C104.2, J6.4 (VDD), U14.1 (OUT)
/SD_CLK: J6.5 (CLK), Module1.57 (SD_CLK)
/SD_CMD: J6.3 (CMD), Module1.62 (SD_CMD)
/SD_DAT0: J6.7 (DAT0), Module1.63 (SD_DAT0)
/SD_DAT1: J6.8 (DAT1), Module1.67 (SD_DAT1)
/SD_DAT2: J6.1 (DAT2), Module1.69 (SD_DAT2)
/SD_DAT3: J6.2 (DAT3/CD), Module1.61 (SD_DAT3)
/SD_PWR_ON: Module1.75 (SD_PWR_ON), R135.2, U14.4 (EN)
/SEL_L1: U10.9 (SEL), U15.28 (PB2)
/SEL_L2_0: U4.35 (CONF0), U12.35 (CONF0), U15.27 (PB1)
/SEL_L2_1: R122.2, U4.36 (CONF1), U12.36 (CONF1), U15.61 (I2C1_SCL)
/SEL_L2_2: R123.2, U4.38 (CONF2), U12.38 (CONF2), U15.62 (I2C1_SDA)
/SEL_L3_0: R126.1, U3.44 (SEL0), U9.44 (SEL0), U15.55 (PB3)
/SEL_L3_1: U3.43 (SEL1), U9.43 (SEL1), U15.56 (PB4)
/SEND_100N: J1.8, U3.37 (D2NA)
/SEND_100P: J1.7, U3.36 (D2PA)
/SEND_101N: J1.18, U3.29 (D2NB)
/SEND_101P: J1.17, U3.28 (D2PB)
/SEND_102N: J1.28, U3.21 (D2NC)
/SEND_102P: J1.27, U3.20 (D2PC)
/SEND_110N: J2.8, U9.37 (D2NA)
/SEND_110P: J2.7, U9.36 (D2PA)
/SEND_111N: J2.18, U9.29 (D2NB)
/SEND_111P: J2.17, U9.28 (D2PB)
/SEND_112N: J2.28, U9.21 (D2NC)
/SEND_112P: J2.27, U9.20 (D2PC)
/SEND_200N: J1.3, U3.41 (D0NA)
/SEND_200P: J1.2, U3.40 (D0PA)
/SEND_201N: J1.13, U3.33 (D0NB)
/SEND_201P: J1.12, U3.32 (D0PB)
/SEND_202N: J1.23, U3.25 (D0NC)
/SEND_202P: J1.22, U3.24 (D0PC)
/SEND_210N: J2.3, U9.41 (D0NA)
/SEND_210P: J2.2, U9.40 (D0PA)
/SEND_211N: J2.13, U9.33 (D0NB)
/SEND_211P: J2.12, U9.32 (D0PB)
/SEND_212N: J2.23, U9.25 (D0NC)
/SEND_212P: J2.22, U9.24 (D0PC)
/SPL_HS_1N: D3.3 (common), R10.1
/SPL_HS_1P: D2.3 (common), R9.1
/SPL_HS_2N: D7.3 (common), R22.1
/SPL_HS_2P: D6.3 (common), R21.1
/SPL_LS_1N: D4.3 (common), U13.5 (+)
/SPL_LS_1P: D1.3 (common), U13.3 (+)
/SPL_LS_2N: D8.3 (common), U13.12 (+)
/SPL_LS_2P: D5.3 (common), U13.10 (+)
/STIM_1N_A: R79.1, U5.10 (IOR2B)
/STIM_1N_B: C2.1, U2.26 (A_TXN)
/STIM_1N_C: C2.2, R11.1
/STIM_1N_R: C51.1, R79.2
/STIM_1N_RC: C51.2, U2.2 (A_RXN)
/STIM_1P_A: R78.1, U5.9 (IOR2A)
/STIM_1P_B: C1.1, U2.27 (A_TXP)
/STIM_1P_C: C1.2, R7.1
/STIM_1P_R: C24.1, R78.2
/STIM_1P_RC: C24.2, U2.1 (A_RXP)
/STIM_2N_A: R81.1, U5.34 (IOR3B)
/STIM_2N_B: C4.1, U2.23 (B_TXN)
/STIM_2N_C: C4.2, R13.1
/STIM_2N_R: C52.1, R81.2
/STIM_2N_RC: C52.2, U2.5 (B_RXN)
/STIM_2P_A: R80.1, U5.11 (IOR3A)
/STIM_2P_B: C3.1, U2.24 (B_TXP)
/STIM_2P_C: C3.2, R14.1
/STIM_2P_R: C50.1, R80.2
/STIM_2P_RC: C50.2, U2.4 (B_RXP)
/STROBE_1N_A: R85.1, U5.13 (IOR10B)
/STROBE_1N_B: C8.1, U2.17 (D_TXN)
/STROBE_1N_C: C8.2, R3.1, R5.1, T13.1
/STROBE_1N_R: C56.1, R85.2
/STROBE_1N_RC: C56.2, U2.11 (D_RXN)
/STROBE_1P_A: R84.1, U5.20 (IOR10A)
/STROBE_1P_B: C7.1, U2.18 (D_TXP)
/STROBE_1P_C: C7.2, R4.2, R6.2, T12.1
/STROBE_1P_R: C55.1, R84.2
/STROBE_1P_RC: C55.2, U2.10 (D_RXP)
/STROBE_2N_A: R83.1, U5.23 (IOR8B)
/STROBE_2N_B: C6.1, U2.20 (C_TXN)
/STROBE_2N_C: C6.2, C70.1, C72.1, C75.2, R17.1, R19.1, R103.1, T14.1, T14.3
/STROBE_2N_R: C54.1, R83.2
/STROBE_2N_RC: C54.2, U2.8 (C_RXN)
/STROBE_2P_A: R82.1, U5.24 (IOR8A)
/STROBE_2P_B: C5.1, U2.21 (C_TXP)
/STROBE_2P_C: C5.2, C70.2, C72.2, C76.2, R18.2, R20.2, R104.1, T15.1, T15.3
/STROBE_2P_R: C53.1, R82.2
/STROBE_2P_RC: C53.2, U2.7 (C_RXP)
/TDR_1N: C66.2, R95.1, U10.4 (A0n)
/TDR_1N_CPL: C66.1, R12.2
/TDR_1P: C61.2, R94.1, U10.3 (A0p)
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
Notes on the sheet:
Selects termination, and flips mesh send/return
to µC ADC
m.2 Standoffs for 2230, 2242, 2260 and 2280
3V3/500mA Digital Supply
Place clip line close to diodes
SoC Activity LED
Signal Splitter
Stimulus & Sampling Pulse Timing Generation
Sub-Mesh Output Mux
Debug connector
Power Supplies
PB10
Sampling Bridges
Pulse Amplifier
PA2
TODO: ESD diodes here?
Debug USB
1V2/100mA Digital Supply
1V5 Digitally Controlled Virtual Ground
Low-Speed Amplifiers
FPGA
Termination Mux & Crossbar
3V3/100mA Analog Supply
Pi CM4/CM5
Clip Lines
Microcontroller
L/R Connector Mux
Couples incident stimulus into mesh, reflections into sampler
M2.5 Standoffs for CM5
PD2
5V/5A System Supply
Mechanical Mounting Holes
m.2 Activity LED
3V3/3A for m.2 NVMe SSD

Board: 2 copper layers, 341 parts (6 on the bottom side), 241 nets, no tracks yet.
